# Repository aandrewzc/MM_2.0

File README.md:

# RAM Mouse 2.0
'17-'18 Micromouse Schematic and PCB Files

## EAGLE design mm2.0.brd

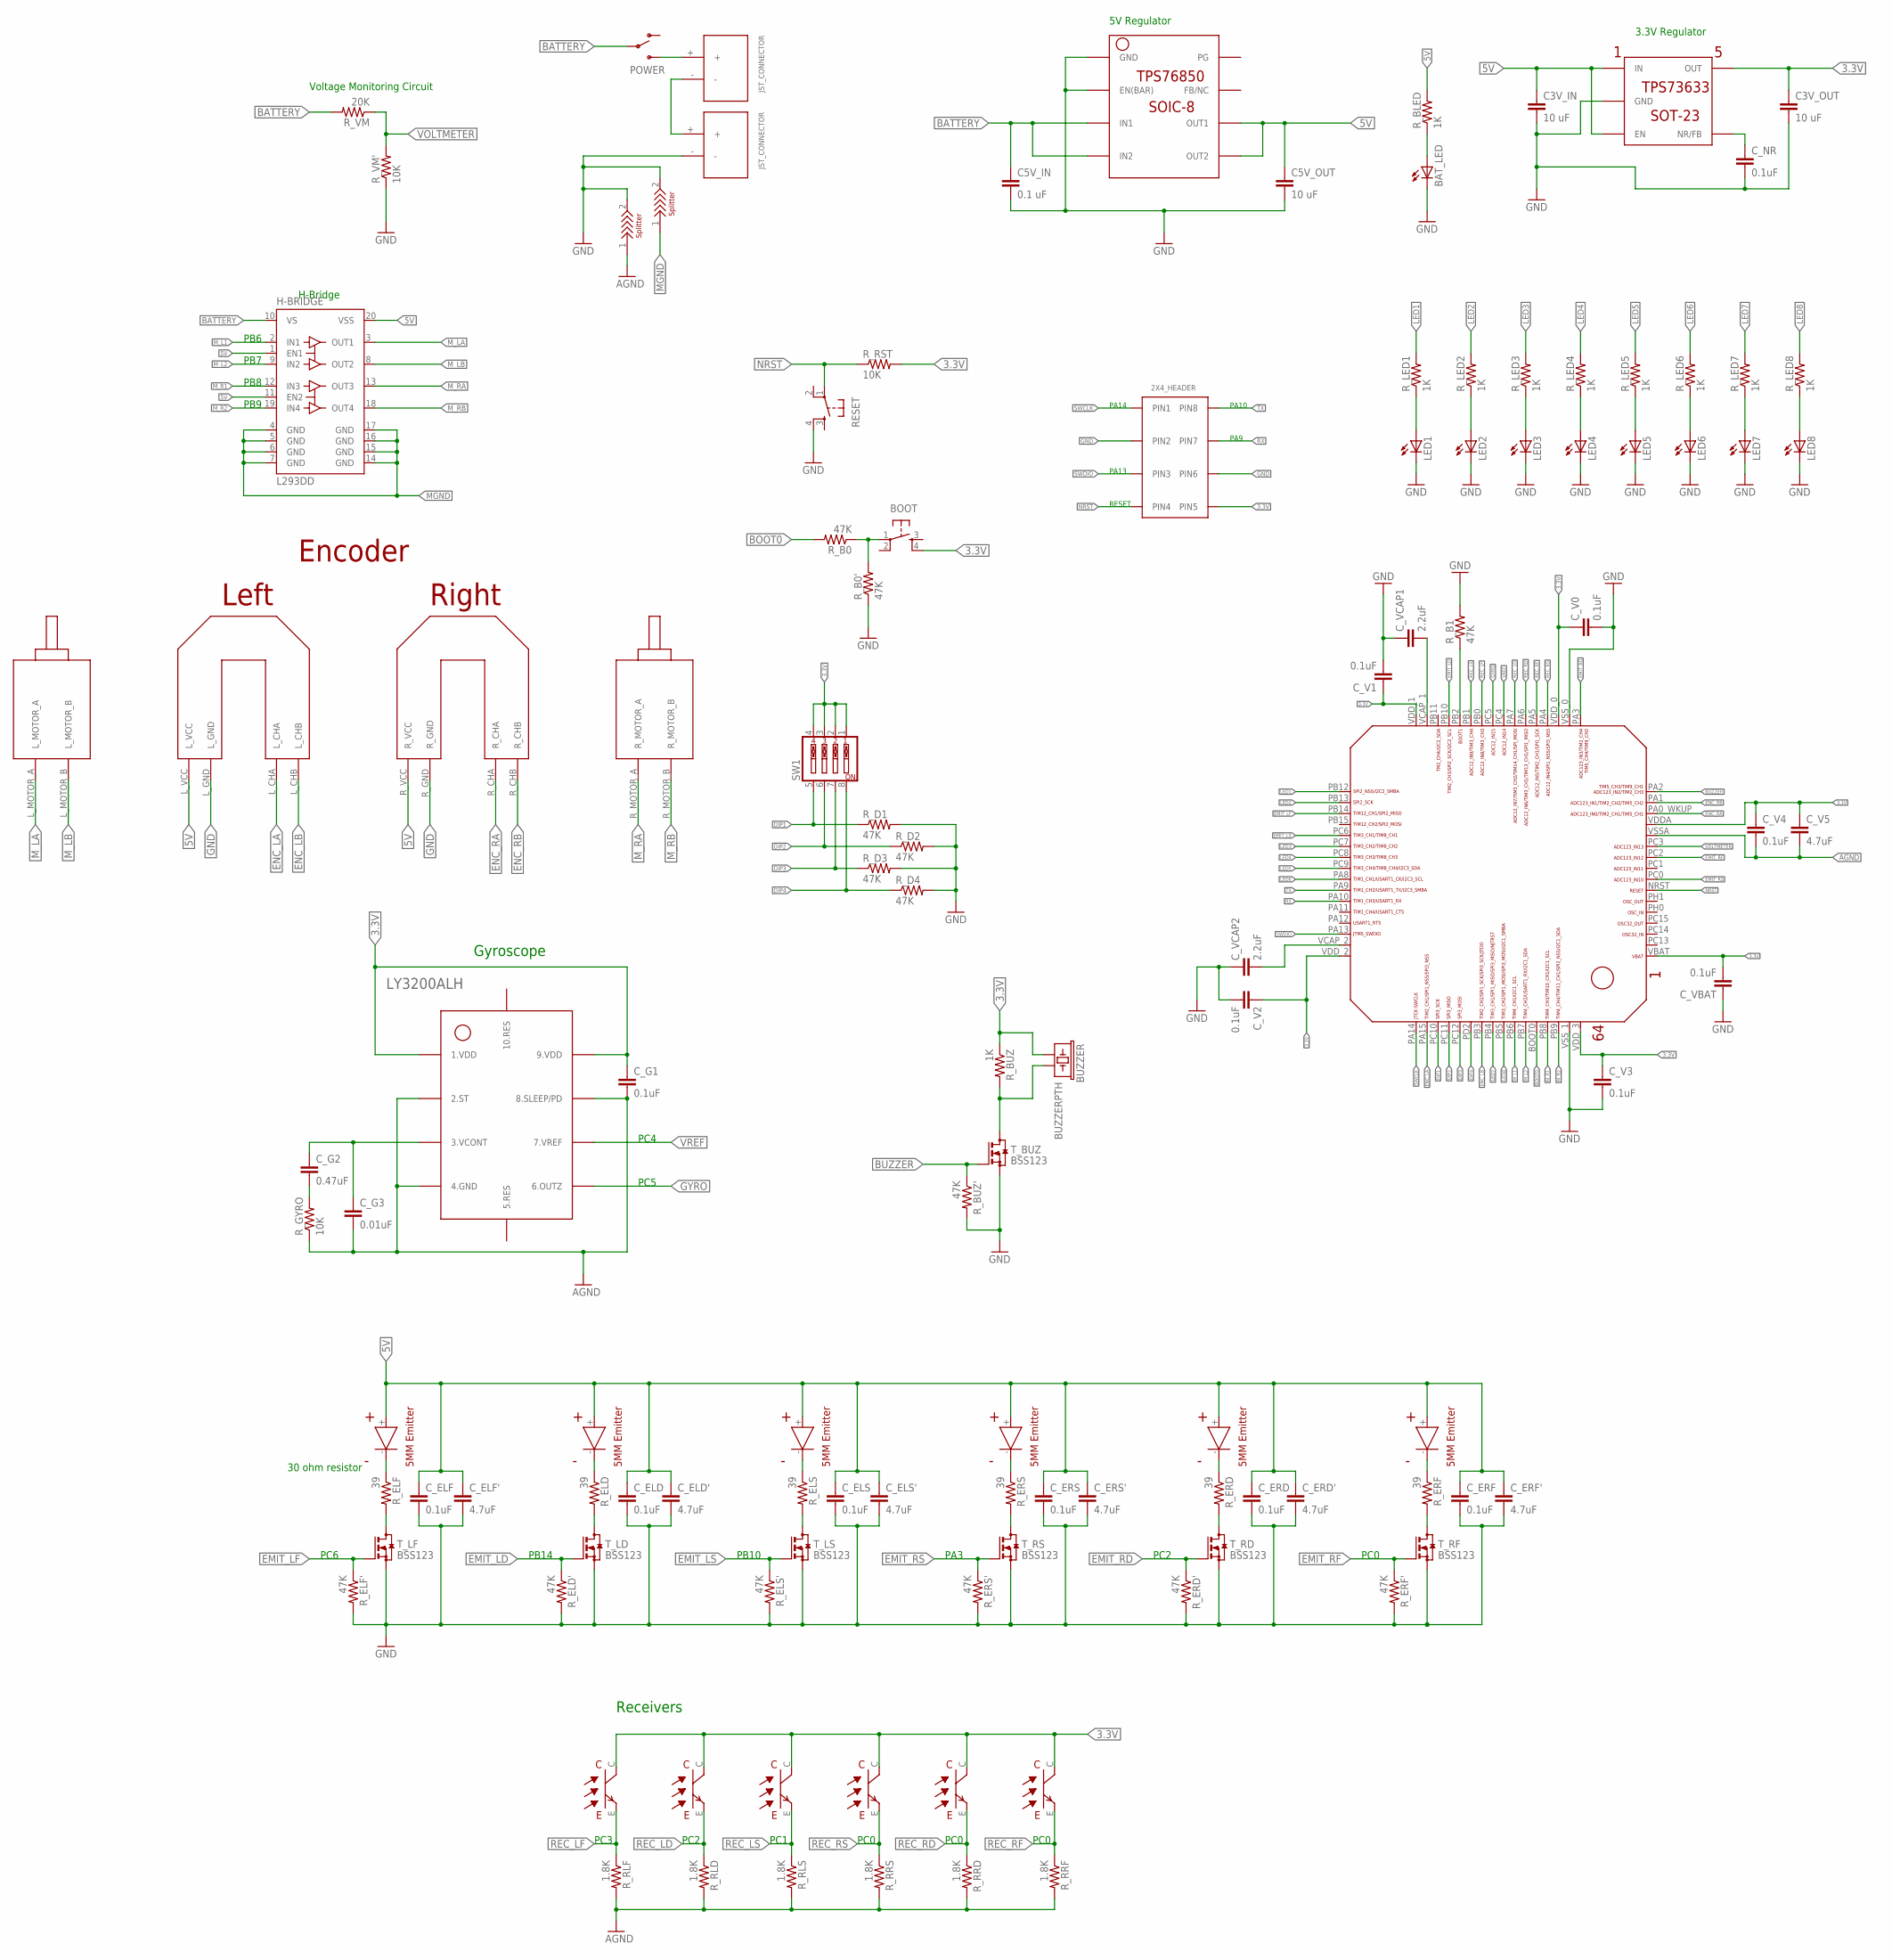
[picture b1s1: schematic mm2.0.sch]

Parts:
BAT_LED: LED1206; LED-1206
BOOT: TAC_SWITCHPTH; TACTILE-PTH
BUZZER: BUZZERPTH; BUZZER-12MM
C3V_IN, C3V_OUT, C5V_OUT: 10 uF; 0603-CAP
C5V_IN: 0.1 uF; 0603-CAP
C_ELD: 0.1uF; 0603-CAP
C_ELD': 4.7uF; 0603-CAP
C_ELF: 0.1uF; 0603-CAP
C_ELF': 4.7uF; 0603-CAP
C_ELS: 0.1uF; 0603-CAP
C_ELS': 4.7uF; 0603-CAP
C_ERD: 0.1uF; 0603-CAP
C_ERD': 4.7uF; 0603-CAP
C_ERF: 0.1uF; 0603-CAP
C_ERF': 4.7uF; 0603-CAP
C_ERS: 0.1uF; 0603-CAP
C_ERS': 4.7uF; 0603-CAP
C_G1: 0.1uF; 0603-CAP
C_G2: 0.47uF; 0603-CAP
C_G3: 0.01uF; 0603-CAP
C_NR: 0.1uF; 0603-CAP
C_V0, C_V1, C_V2, C_V3, C_V4: 0.1uF; 0603-CAP
C_V5: 4.7uF; 0603-CAP
C_VBAT: 0.1uF; 0603-CAP
C_VCAP1, C_VCAP2: 2.2uF; 0603-CAP
H-BRIDGE: L293DD; SO20
IR_LD: EMITTER
IR_LF: EMITTER
IR_LS: EMITTER
IR_RD: EMITTER
IR_RF: EMITTER
IR_RS: EMITTER
JST: A; JST_CONNECTOR_FEMALE
LED1, LED2, LED3, LED4, LED5, LED6, LED7, LED8: LEDSML0603; SML0603
MCU/BLU: 2X3_HEADER
POWER: SWITCH-SPDTPTH; SWITCH-SPDT
REC_LD: RECEIVER
REC_LF: RECEIVER
REC_LS: RECEIVER
REC_RD: RECEIVER
REC_RF: RECEIVER
REC_RS: RECEIVER
RESET: TAC_SWITCHPTH; TACTILE-PTH
R_B0, R_B0', R_B1: 47K; 0603-RES
R_BLED: 1K; 0603-RES
R_BUZ: 1K; 0603-RES
R_BUZ': 47K; 0603-RES
R_D1, R_D2, R_D3, R_D4: 47K; 0603-RES
R_ELD: 39; 0603-RES
R_ELD': 47K; 0603-RES
R_ELF: 39; 0603-RES
R_ELF': 47K; 0603-RES
R_ELS: 39; 0603-RES
R_ELS': 47K; 0603-RES
R_ERD: 39; 0603-RES
R_ERD': 47K; 0603-RES
R_ERF: 39; 0603-RES
R_ERF': 47K; 0603-RES
R_ERS: 39; 0603-RES
R_ERS': 47K; 0603-RES
R_GYRO: 10K; 0603-RES
R_LED1, R_LED2, R_LED3, R_LED4, R_LED5, R_LED6, R_LED7, R_LED8: 1K; 0603-RES
R_RLD: 1.8K; 0603-RES
R_RLF: 1.8K; 0603-RES
R_RLS: 1.8K; 0603-RES
R_RRD: 1.8K; 0603-RES
R_RRF: 1.8K; 0603-RES
R_RRS: 1.8K; 0603-RES
R_RST: 10K; 0603-RES
R_VM: 20K; 0603-RES
R_VM': 10K; 0603-RES
SW1: SW_DIP-4; EDG-04
T_BUZ: BSS123; SOT23
T_LD: BSS123; SOT23
T_LF: BSS123; SOT23
T_LS: BSS123; SOT23
T_RD: BSS123; SOT23
T_RF: BSS123; SOT23
T_RS: BSS123; SOT23
U$1: JST_CONNECTOR_FEMALE
U$2: TPS73633(SOT-23)
U$3: TPS76850(SOIC-8)
U$4: STM32F405/415_LQFP64
U$5: FUTURA_V1.0_MOTOR_MOUNT; FUTURA_V1.0_MOTOT_MOUNT
U$6: LY3200ALH
U$19, U$20: SPLITTER

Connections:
3.3V: BOOT.4, BUZZER.+ (1), C3V_OUT.1, C_G1.1, C_V0.1, C_V1.1, C_V2.1, C_V3.1, C_V4.1, C_V5.1, C_VBAT.2, MCU/BLU.PIN5, REC_LD.C, REC_LF.C, REC_LS.C, REC_RD.C, REC_RF.C, REC_RS.C, R_BUZ.1, R_RST.2, SW1.1, SW1.2, SW1.3, SW1.4, U$2.OUT, U$4.VBAT, U$4.VDDA, U$4.VDD_0, U$4.VDD_1, U$4.VDD_2, U$4.VDD_3, U$6.1.VDD@1 (1.VDD), U$6.9.VDD@2 (9.VDD)
5V: C3V_IN.1, C5V_OUT.1, C_ELD.1, C_ELD'.1, C_ELF.1, C_ELF'.1, C_ELS.1, C_ELS'.1, C_ERD.1, C_ERD'.1, C_ERF.1, C_ERF'.1, C_ERS.1, C_ERS'.1, H-BRIDGE.1 (EN1), H-BRIDGE.11 (EN2), H-BRIDGE.20 (VSS), IR_LD.+, IR_LF.+, IR_LS.+, IR_RD.+, IR_RF.+, IR_RS.+, R_BLED.2, U$2.EN, U$2.IN, U$3.OUT1, U$3.OUT2, U$5.L_VCC, U$5.R_VCC
AGND: C_G1.2, C_G3.2, C_V4.2, C_V5.2, R_GYRO.1, R_RLD.2, R_RLF.2, R_RLS.2, R_RRD.2, R_RRF.2, R_RRS.2, U$4.VSSA, U$6.2.ST, U$6.4.GND, U$6.8.SLEEP/PD, U$19.1
BATTERY: C5V_IN.1, H-BRIDGE.10 (VS), POWER.2, R_VM.2, U$3.IN1, U$3.IN2
BOOT0: R_B0.2, U$4.BOOT0
BUZZER: R_BUZ'.1, T_BUZ.1 (G), U$4.PA2
C_NR: C_NR.1, U$2.NR/FB
DIP1: R_D1.1, SW1.5, U$4.PC10
DIP2: R_D2.1, SW1.6, U$4.PC11
DIP3: R_D3.1, SW1.7, U$4.PC12
DIP4: R_D4.1, SW1.8, U$4.PD2
EMIT_LD: R_ELD'.1, T_LD.1 (G), U$4.PB10
EMIT_LF: R_ELF'.1, T_LF.1 (G), U$4.PB14
EMIT_LS: R_ELS'.1, T_LS.1 (G), U$4.PC6
EMIT_RD: R_ERD'.1, T_RD.1 (G), U$4.PA3
EMIT_RF: R_ERF'.1, T_RF.1 (G), U$4.PC2
EMIT_RS: R_ERS'.1, T_RS.1 (G), U$4.PC0
ENC_LA: U$4.PA15, U$5.L_CHA
ENC_LB: U$4.PB3, U$5.L_CHB
ENC_RA: U$4.PA0_WKUP (PA0_AKUP), U$5.R_CHA
ENC_RB: U$4.PA1, U$5.R_CHB
GND: BAT_LED.C, C3V_IN.2, C3V_OUT.2, C5V_IN.2, C5V_OUT.2, C_ELD.2, C_ELD'.2, C_ELF.2, C_ELF'.2, C_ELS.2, C_ELS'.2, C_ERD.2, C_ERD'.2, C_ERF.2, C_ERF'.2, C_ERS.2, C_ERS'.2, C_NR.2, C_V0.2, C_V1.2, C_V2.2, C_V3.2, C_VBAT.1, C_VCAP1.1, C_VCAP2.1, LED1.C, LED2.C, LED3.C, LED4.C, LED5.C, LED6.C, LED7.C, LED8.C, MCU/BLU.PIN2, MCU/BLU.PIN6, RESET.4, R_B0'.1, R_B1.2, R_BUZ'.2, R_D1.2, R_D2.2, R_D3.2, R_D4.2, R_ELD'.2, R_ELF'.2, R_ELS'.2, R_ERD'.2, R_ERF'.2, R_ERS'.2, R_VM'.1, T_BUZ.2 (S), T_LD.2 (S), T_LF.2 (S), T_LS.2 (S), T_RD.2 (S), T_RF.2 (S), T_RS.2 (S), U$1.-, U$2.GND, U$3.EN(BAR), U$3.GND, U$4.VSS_0, U$4.VSS_1, U$5.L_GND, U$5.R_GND, U$19.2, U$20.2
GYRO: U$4.PC5, U$6.6.OUTZ
GY_C-R: C_G2.2, R_GYRO.2
IR1: IR_LF.-, R_ELF.1
IR2: IR_LD.-, R_ELD.1
IR3: IR_LS.-, R_ELS.1
IR4: IR_RS.-, R_ERS.1
IR5: IR_RD.-, R_ERD.1
IR6: IR_RF.-, R_ERF.1
JST: JST.-, U$1.+
L1: LED1.A, R_LED1.1
L2: LED2.A, R_LED2.1
L3: LED3.A, R_LED3.1
L4: LED4.A, R_LED4.1
L5: LED5.A, R_LED5.1
L6: LED6.A, R_LED6.1
L7: LED7.A, R_LED7.1
L8: LED8.A, R_LED8.1
LED1: R_LED1.2, U$4.PB12
LED2: R_LED2.2, U$4.PB13
LED3: R_LED3.2, U$4.PC7
LED4: R_LED4.2, U$4.PC8
LED5: R_LED5.2, U$4.PC9
LED6: R_LED6.2, U$4.PA8
LED7: R_LED7.2, U$4.PB4
LED8: R_LED8.2, U$4.PB5
LEDB: BAT_LED.A, R_BLED.1
MGND: H-BRIDGE.4 (GND), H-BRIDGE.5 (GND), H-BRIDGE.6 (GND), H-BRIDGE.7 (GND), H-BRIDGE.14 (GND), H-BRIDGE.15 (GND), H-BRIDGE.16 (GND), H-BRIDGE.17 (GND), U$20.1
M_L1: H-BRIDGE.2 (IN1), U$4.PB6
M_L2: H-BRIDGE.9 (IN2), U$4.PB7
M_LA: H-BRIDGE.3 (OUT1), U$5.L_MOTOR_A
M_LB: H-BRIDGE.8 (OUT2), U$5.L_MOTOR_B
M_R1: H-BRIDGE.12 (IN3), U$4.PB8
M_R2: H-BRIDGE.19 (IN4), U$4.PB9
M_RA: H-BRIDGE.13 (OUT3), U$5.R_MOTOR_A
M_RB: H-BRIDGE.18 (OUT4), U$5.R_MOTOR_B
NRST: MCU/BLU.PIN4, RESET.1, R_RST.1, U$4.NRST
PB2: R_B1.1, U$4.PB2
REC_LD: REC_LD.E, R_RLD.1, U$4.PA7
REC_LF: REC_LF.E, R_RLF.1, U$4.PB0
REC_LS: REC_LS.E, R_RLS.1, U$4.PB1
REC_RD: REC_RD.E, R_RRD.1, U$4.PA6
REC_RF: REC_RF.E, R_RRF.1, U$4.PA5
REC_RS: REC_RS.E, R_RRS.1, U$4.PA4
RX: MCU/BLU.PIN7, U$4.PA10
R_BOOT: BOOT.1, R_B0.1, R_B0'.2
SWCLK: MCU/BLU.PIN1, U$4.PA14
SWDIO: MCU/BLU.PIN3, U$4.PA13
SWITCH: JST.+, POWER.3 (S)
TX: MCU/BLU.PIN8, U$4.PA9
T_BUZ: BUZZER.- (2), R_BUZ.2, T_BUZ.3 (D)
T_LD: R_ELD.2, T_LD.3 (D)
T_LF: R_ELF.2, T_LF.3 (D)
T_LS: R_ELS.2, T_LS.3 (D)
T_RD: R_ERD.2, T_RD.3 (D)
T_RF: R_ERF.2, T_RF.3 (D)
T_RS: R_ERS.2, T_RS.3 (D)
VCONT: C_G2.1, C_G3.1, U$6.3.VCONT
VOLTMETER: R_VM.1, R_VM'.2, U$4.PC3
VREF: U$4.PC4, U$6.7.VREF
V_C1: C_VCAP1.2, U$4.VCAP_1
V_C2: C_VCAP2.2, U$4.VCAP_2

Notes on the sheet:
5V Regulator
3.3V Regulator
H-Bridge
Voltage Monitoring Circuit
PA14
PA13
Gyroscope
RESET
30 ohm resistor
PC5
PB6
PB7
PB8
PB9
PC6
PB14
PB10
PA3
PC2
PC0
PC3
PC1
Receivers
PC4
PA9
PA10

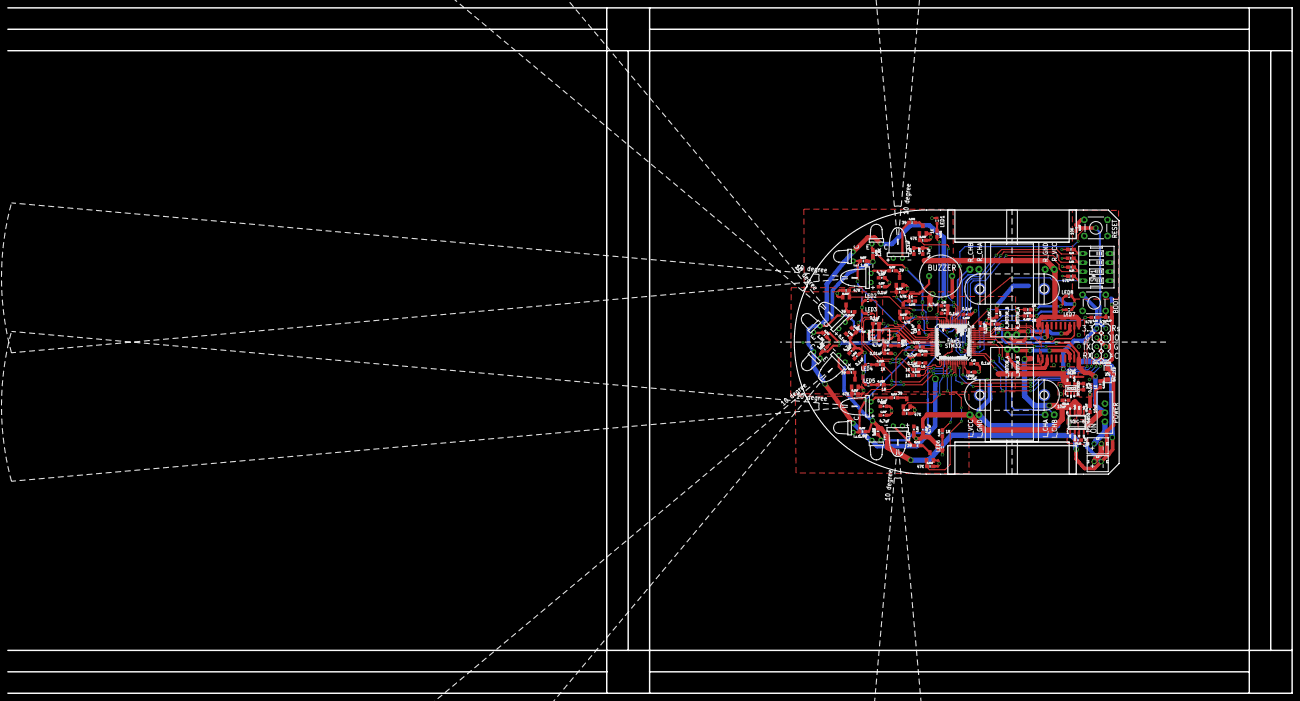
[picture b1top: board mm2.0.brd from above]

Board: 2 copper layers, 192.0 x 192.0 mm, 113 parts (0 on the bottom side), 83 nets.

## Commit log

2017-11-22 testing git commit
2017-11-25 Named passives
2017-11-26 placing parts
2017-11-26 placed all parts
2017-11-26 added some polygons and traces
2017-11-27 adding more traces
2017-11-27 33 airwires remaining
2017-11-27 27 airwires remaining
2017-11-27 NO airwires left
2017-11-27 Fixed an LED trace
2017-11-30 cleaned up traces
2017-12-02 Post-Design Review Updates

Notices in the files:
parts and their libraries:
SparkFun: Licensing: CC v3.0 Share-Alike You are welcome to use this library for commercial purposes.
SparkFun-Retired: Licensing:Creative Commons ShareAlike 4.0 International - https://creativecommons.org/licenses/by-sa/4.0
